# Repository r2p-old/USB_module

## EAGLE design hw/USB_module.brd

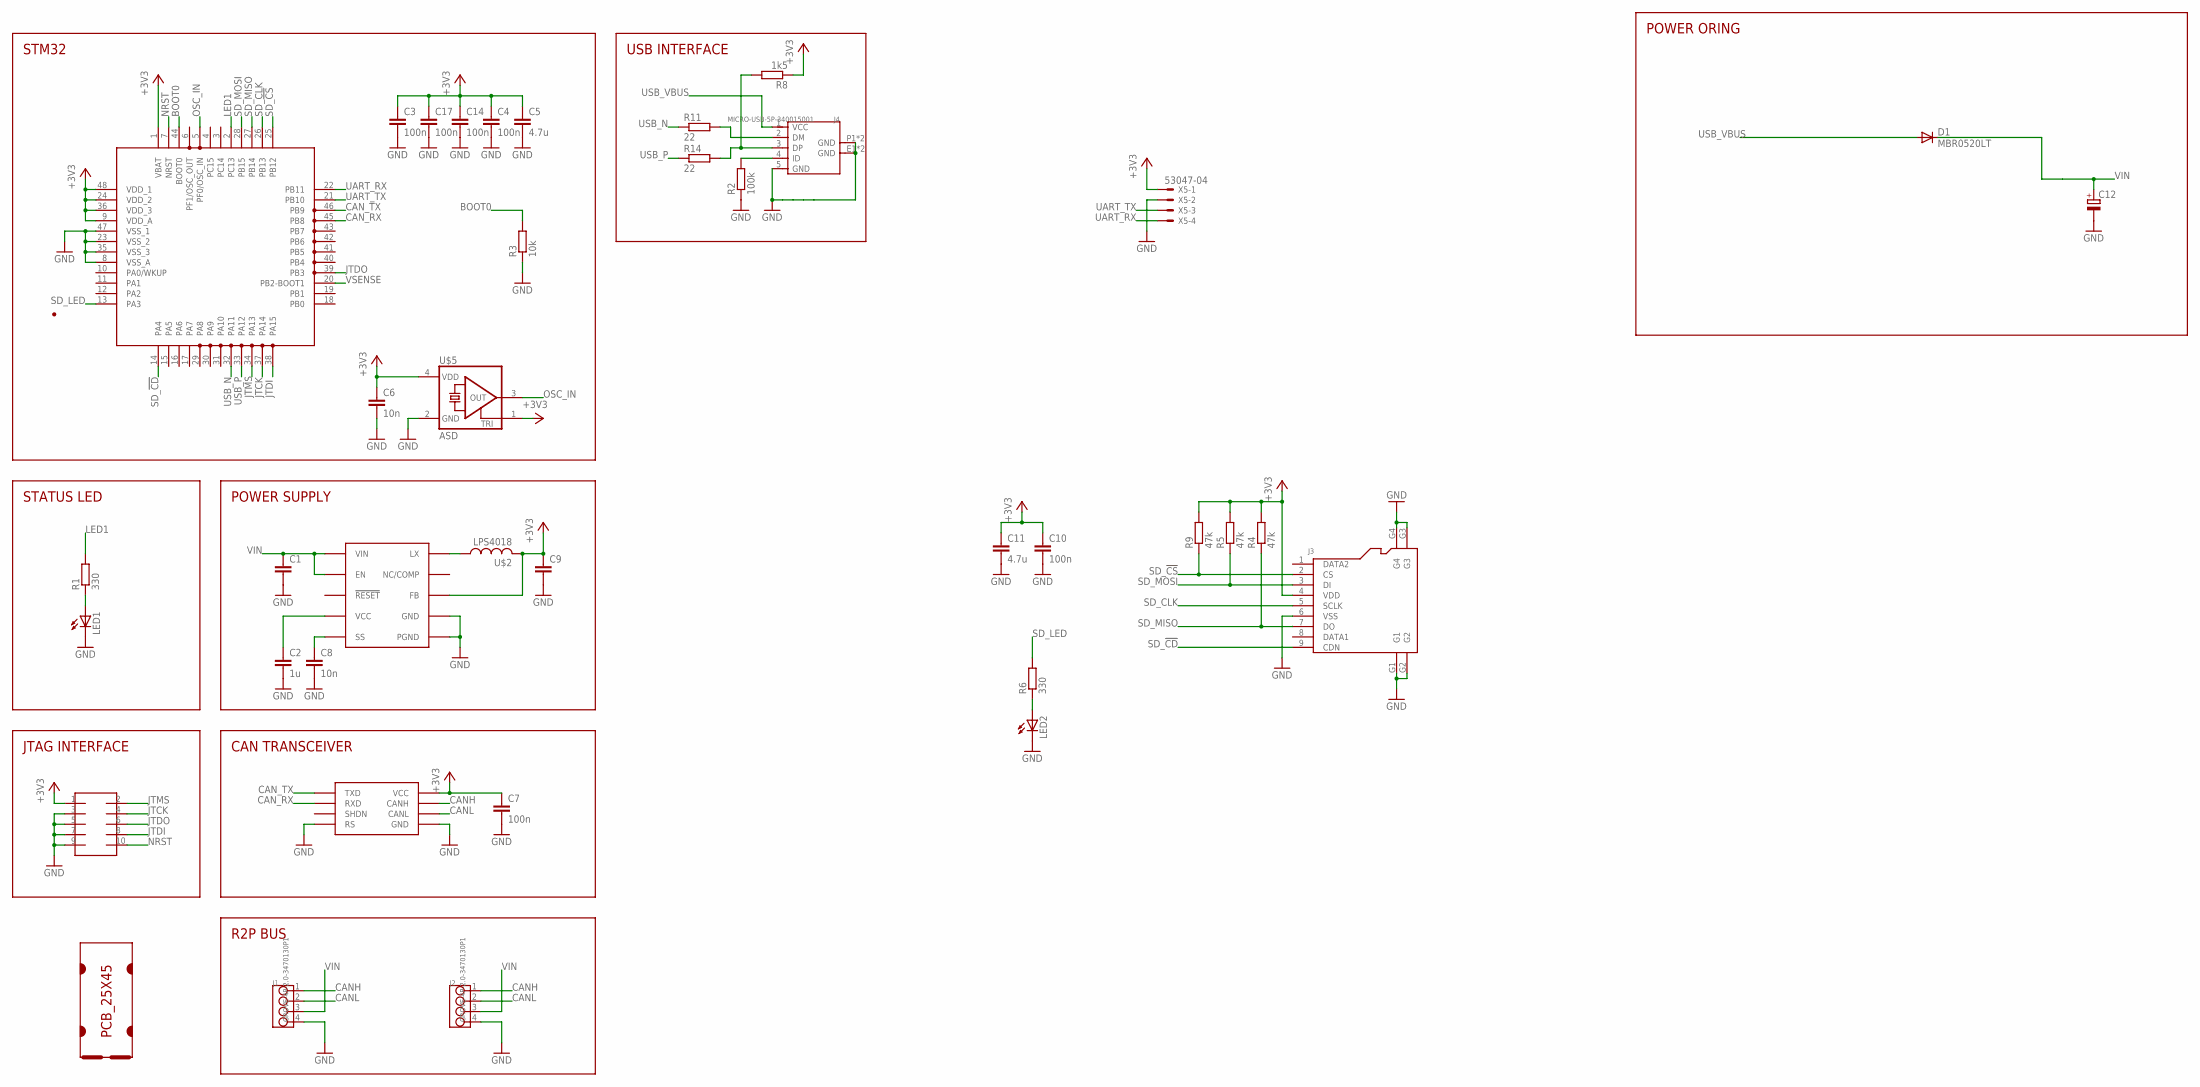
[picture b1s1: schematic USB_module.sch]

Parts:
C1: C-EUC1206; C1206
C2: 1u; C0603
C3, C4, C7, C10, C14, C17: 100n; C0603
C5, C11: 4.7u; C0805
C6, C8: 10n; C0603
C9: C-EUC0805; C0805
C12: CPOL-EUB/3528-21R; B/3528-21R
D1: MBR0520LT; SOD123
J1, J2: GROVE-4P-2.0-3470130P1; 4P-2.0
J3: MICRO-SD-CARD-HOLDER-9P'MICROSD-9P'; 9+4P-SMD-L16.1*W14.5*H1.85MM
J4: MICRO-USB-5P-340015001; B-SMD-5P
LED1, LED2: LEDCHIPLED_0805; CHIPLED_0805
R1, R6: 330; R0603
R2: 100k; R0603
R3: 10k; R0603
R4, R5, R9: 47k; R0603
R8: 1k5; R0603
R11, R14: 22; R0603
SOT1: MAX3051EKA; SOT23-8L
U$1: PCB_25X45; 25X45
U$2: LPS4018
U$3: MAX17501; TDFN-10
U$4: FTSH-105TH; FTSH-105-TH
U$5: ASD; 2.5X2
U$6: STM32F303C; LQFP48
X5: 53047-04

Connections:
+3V3: C3.1, C4.1, C5.1, C6.1, C7.1, C9.1, C10.1, C11.1, C14.1, C17.1, J3.4 (VDD), R4.2, R5.2, R8.1, R9.2, SOT1.3 (VCC), U$2.P$2 (2), U$3.P$5 (FB), U$4.1, U$5.1 (TRI), U$5.4 (VDD), U$6.1 (VBAT), U$6.9 (VDD_A), U$6.24 (VDD_2), U$6.36 (VDD_3), U$6.48 (VDD_1), X5.1
BOOT0: R3.2, U$6.44 (BOOT0)
CANH: J1.1, J2.1, SOT1.7 (CANH)
CANL: J1.2, J2.2, SOT1.6 (CANL)
CAN_RX: SOT1.4 (RXD), U$6.45 (PB8)
CAN_TX: SOT1.1 (TXD), U$6.46 (PB9)
GND: C1.2, C2.2, C3.2, C4.2, C5.2, C6.2, C7.2, C8.2, C9.2, C10.2, C11.2, C12.-, C14.2, C17.2, J1.4, J2.4, J3.6 (VSS), J3.G1, J3.G2, J3.G3, J3.G4, J4.5 (GND), J4.E1 (GND), J4.E2 (GND), J4.P1 (GND), J4.P2 (GND), LED1.C, LED2.C, R2.1, R3.1, SOT1.2 (GND), SOT1.8 (RS), U$3.P$1 (PGND), U$3.P$9 (GND), U$3.P$11 (PGND), U$4.3, U$4.5, U$4.7, U$4.9, U$5.2 (GND), U$6.8 (VSS_A), U$6.23 (VSS_2), U$6.35 (VSS_3), U$6.47 (VSS_1), X5.2
JTCK: U$4.4, U$6.37 (PA14)
JTDI: U$4.8, U$6.38 (PA15)
JTDO: U$4.6, U$6.39 (PB3)
JTMS: U$4.2, U$6.34 (PA13)
LED1: R1.2, U$6.2 (PC13)
unnamed: U$2.P$1 (1), U$3.P$10 (LX)
unnamed: J4.2 (DM), R11.2
unnamed: LED1.A, R1.1
unnamed: J4.4 (ID), R2.2
unnamed: LED2.A, R6.1
unnamed: C2.1, U$3.P$4 (VCC)
unnamed: C8.1, U$3.P$6 (SS)
unnamed: J4.3 (DP), R8.2, R14.2
NRST: U$4.10, U$6.7 (NRST)
OSC_IN: U$5.3 (OUT), U$6.5 (PF0/OSC_IN)
SD_!CD: J3.9 (CDN), U$6.14 (PA4)
SD_!CS: J3.2 (CS), R9.1, U$6.25 (PB12)
SD_CLK: J3.5 (SCLK), U$6.26 (PB13)
SD_LED: R6.2, U$6.13 (PA3)
SD_MISO: J3.7 (DO), R4.1, U$6.27 (PB14)
SD_MOSI: J3.3 (DI), R5.1, U$6.28 (PB15)
UART_RX: U$6.22 (PB11), X5.4
UART_TX: U$6.21 (PB10), X5.3
USB_N: R11.1, U$6.32 (PA11)
USB_P: R14.1, U$6.33 (PA12)
USB_VBUS: D1.A, J4.1 (VCC)
VIN: C1.1, C12.+, D1.C, J1.3, J2.3, U$3.P$2 (VIN), U$3.P$3 (EN)
VSENSE: U$6.20 (PB2-BOOT1)

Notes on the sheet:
STM32
STATUS LED
JTAG INTERFACE
POWER SUPPLY
CAN TRANSCEIVER
R2P BUS
USB INTERFACE
POWER ORING

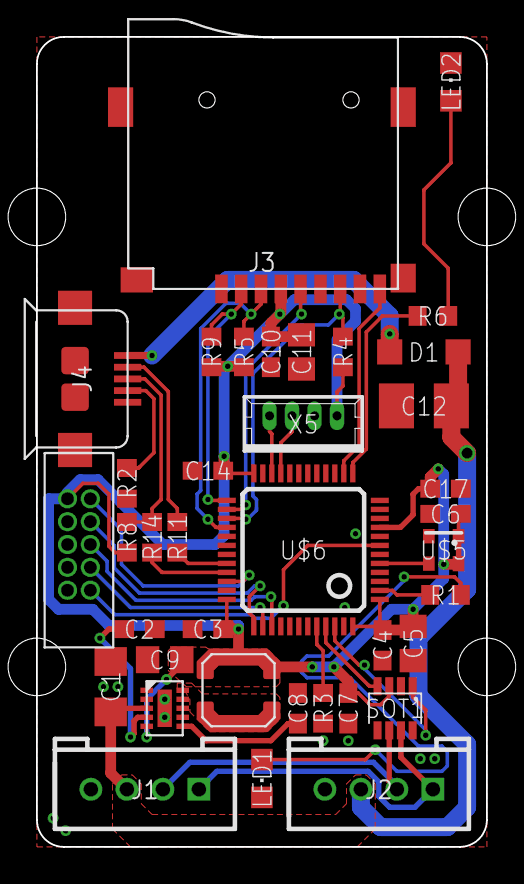
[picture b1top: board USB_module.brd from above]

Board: 2 copper layers, 25.0 x 45.0 mm, 39 parts (0 on the bottom side), 34 nets.

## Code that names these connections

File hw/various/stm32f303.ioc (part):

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Mcu.Name=STM32F303C(B-C)Tx
Mcu.Package=LQFP48
Mcu.UserName=STM32F303CBTx
PA10.Mode=I2C
PA10.Signal=I2C2_SDA
PA11.Mode=Dummy
PA11.Signal=USB_DM
PA12.Mode=Dummy
PA12.Signal=USB_DP
PA13.Mode=JTAG(4-pin)
PA13.Signal=SYS_JTMS-SWDIO
PA14.Mode=JTAG(4-pin)
PA14.Signal=SYS_JTCK-SWCLK
PA15.Mode=JTAG(4-pin)
PA15.Signal=SYS_JTDI
PA9.Mode=I2C
PA9.Signal=I2C2_SCL
PB10.Mode=Asynchronous
PB10.Signal=USART3_TX
PB11.Mode=Asynchronous
PB11.Signal=USART3_RX
PB12.Mode=NSS_Signal_Hard
PB12.Signal=SPI2_NSS
PB13.Mode=Full_Duplex_Master
PB13.Signal=SPI2_SCK
PB14.Mode=Full_Duplex_Master
PB14.Signal=SPI2_MISO
PB15.Mode=Full_Duplex_Master
PB15.Signal=SPI2_MOSI
PB3.Mode=JTAG(4-pin)
PB3.Signal=SYS_JTDO-TRACESWO
PB8.Mode=Master
PB8.Signal=CAN_RX
PB9.Mode=Master
PB9.Signal=CAN_TX
PF0-OSC_IN.Signal=SYS_OSC_IN
PF1-OSC_OUT.GPIOParameters=GPIO_Label
PF1-OSC_OUT.GPIO_Label=LED
PF1-OSC_OUT.Signal=GPIO_Output

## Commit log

2014-06-06 work in progress
2014-06-09 layout of power oring section ongoing
2014-06-10 layout almost finished
2014-06-10 layout completed
2014-06-11 added silkscreen
2014-06-23 Added makefile for quicker gerber generation
2014-06-24 fixed silkscreen
2014-08-01 updated USB R value
2014-12-04 updated to eagle 7.2
2014-12-05 layout complete
2014-12-16 small fixes for production
2014-12-16 small fixes
2014-12-29 approved DRC false errors
2015-01-08 added logo to bottom silkscreen
2015-01-13 minor fixes for manufacturing
2015-01-24 added assembly PDF generation
2015-03-23 Grounded uSD shield
2015-03-23 Changed layout PNG background color
